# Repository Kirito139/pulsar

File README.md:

Pulsar is a rather simple (its my first ever hardware project) macropad which I made for [highway.hackclub.com](highway.hackclub.com). It features a 3x3 electrical matrix arranged into a 2x4 key grid and a rotary encoder. There's also an OLED display and two NeoPixels! Rather simple design but I'll probably come back and improve it sometime.

# Images

# BOM
I will 3d print the case myself.

Here's the BOM that KiCad generated:

|   |   |   |   |   |   |   |   |
|---|---|---|---|---|---|---|---|
|**Reference**|**Qty**|**Value**|**DNP**|**Exclude from BOM**|**Exclude from Board**|**Footprint**|**Datasheet**|
|**D1,D2**|2|SK6812MINI||||LED_SMD:LED_SK6812MINI_PLCC4_3.5x3.5mm_P1.75mm|[https://cdn-shop.adafruit.com/product-files/2686/SK6812MINI_REV.01-1-2.pdf](https://cdn-shop.adafruit.com/product-files/2686/SK6812MINI_REV.01-1-2.pdf)|
|**D3,D4,D5,D6,D7,D8,D9,D10,D11**|9|1N4148||||Diode_THT:D_DO-35_SOD27_P7.62mm_Horizontal|[https://assets.nexperia.com/documents/data-sheet/1N4148_1N4448.pdf](https://assets.nexperia.com/documents/data-sheet/1N4148_1N4448.pdf)|
|**J1**|1|Conn_01x04_Pin||||hackpad:SSD1306-0.91-OLED-4pin-128x32|~|
|**SW1,SW2,SW3,SW4,SW5,SW7,SW8,SW9**|8|SW_Push||||Button_Switch_Keyboard:SW_Cherry_MX_1.00u_PCB|~|
|**SW6**|1|RotaryEncoder_Switch||||Rotary_Encoder:RotaryEncoder_Alps_EC11E-Switch_Vertical_H20mm|~|
|**U1**|1|XIAO-RP2040-DIP||||OPL:XIAO-RP2040-DIP||

I will also need 4 m3.5 screws

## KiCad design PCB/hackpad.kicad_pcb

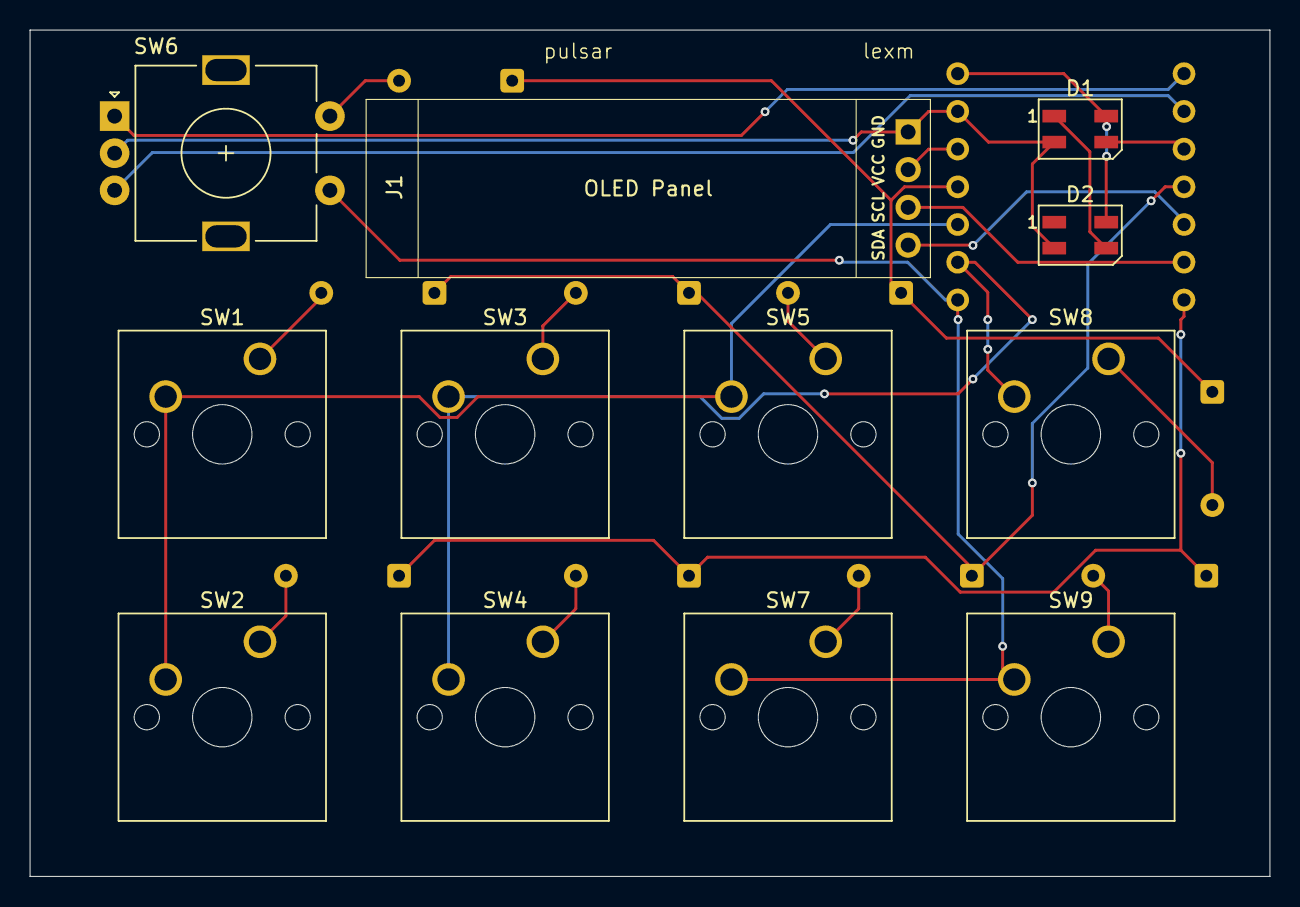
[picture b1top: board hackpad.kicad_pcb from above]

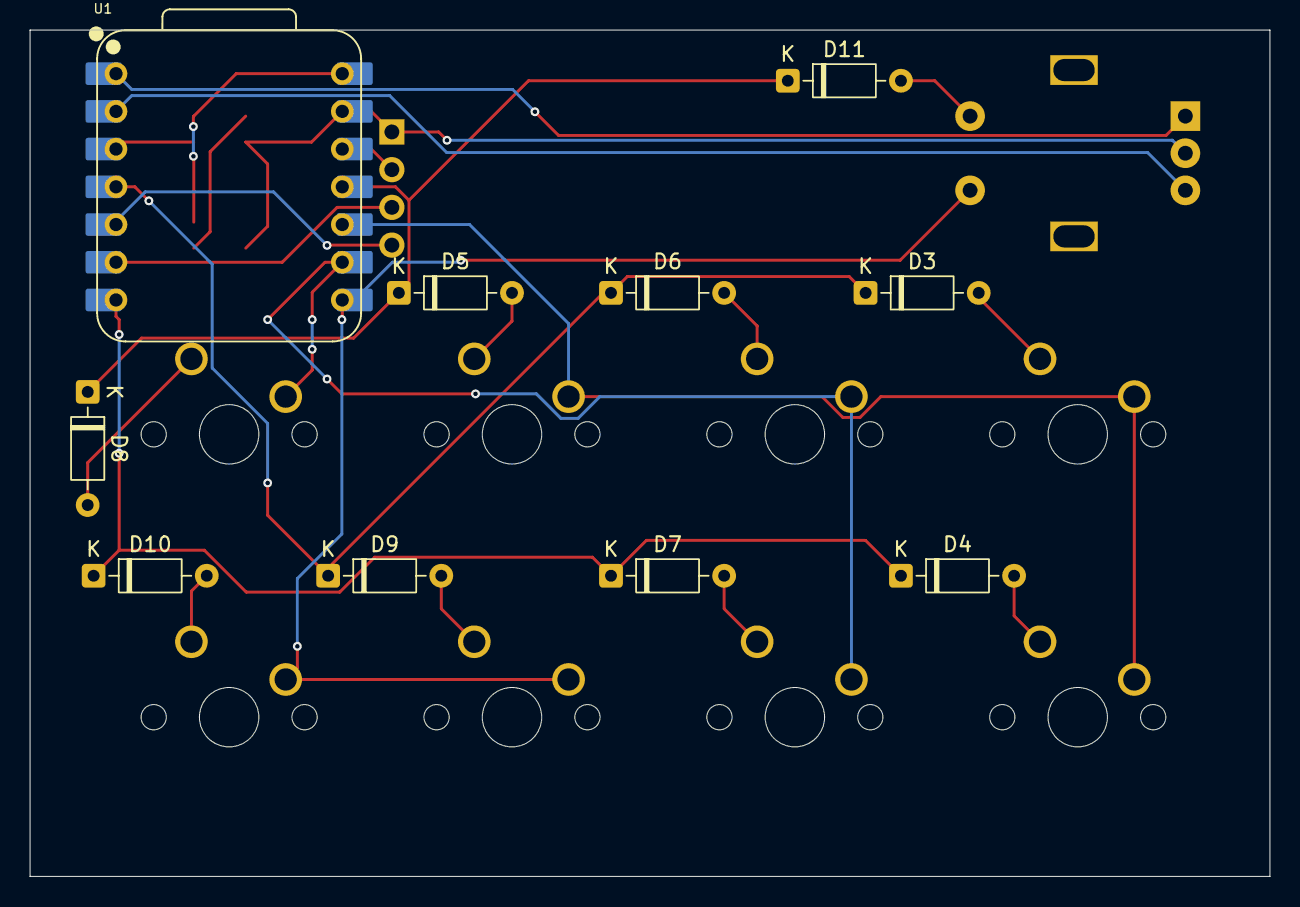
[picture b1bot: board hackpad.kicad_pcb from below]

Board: 2 copper layers, 83.5 x 57.0 mm, 22 parts (10 on the bottom side), 24 nets.

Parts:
D1, D2: SK6812MINI; LED_SK6812MINI_PLCC4_3.5x3.5mm_P1.75mm
D3, D4, D5, D6, D7, D8, D9, D10, D11: 1N4148; D_DO-35_SOD27_P7.62mm_Horizontal
J1: Conn_01x04_Pin; SSD1306-0.91-OLED-4pin-128x32
SW1, SW2, SW3, SW4, SW5, SW7, SW8, SW9: SW_Push; SW_Cherry_MX_1.00u_PCB
SW6: RotaryEncoder_Switch; RotaryEncoder_Alps_EC11E-Switch_Vertical_H20mm
U1: XIAO-RP2040-DIP

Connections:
+3V3: J1.2, U1.12 (3V3)
+5V: D1.4 (VDD), D2.4 (VDD), U1.14 (VBUS)
C1: SW1.2, SW2.2, SW5.2, U1.10 (GPIO4/MISO)
C2: SW3.2, SW4.2, SW8.2, U1.9 (GPIO2/SCK)
C3: SW6.S1, SW7.2, SW9.2, U1.8 (GPIO1/RX)
GND: D1.2 (VSS), D2.2 (VSS), J1.1, SW6.C, U1.13 (GND)
unnamed: D1.3 (DIN), U1.3 (GPIO28/ADC2/A2)
unnamed: D1.1 (DOUT), D2.3 (DIN)
unnamed: D3.2 (A), SW1.1
unnamed: D4.2 (A), SW2.1
unnamed: D5.2 (A), SW5.1
unnamed: D6.2 (A), SW3.1
unnamed: D7.2 (A), SW4.1
unnamed: D8.2 (A), SW8.1
unnamed: D9.2 (A), SW7.1
unnamed: D10.2 (A), SW9.1
unnamed: J1.3, U1.6 (GPIO7/SCL)
unnamed: J1.4, U1.5 (GPIO6/SDA)
unnamed: SW6.A, U1.1 (GPIO26/ADC0/A0)
unnamed: SW6.B, U1.2 (GPIO27/ADC1/A1)
R1: D3.1 (K), D6.1 (K), D9.1 (K), U1.4 (GPIO29/ADC3/A3)
R2: D4.1 (K), D7.1 (K), D10.1 (K), U1.7 (GPIO0/TX)
R3: D5.1 (K), D8.1 (K), D11.1 (K), U1.11 (GPIO3/MOSI)
ROT_B: D11.2 (A), SW6.S2

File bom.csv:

"Reference","Qty","Value","DNP","Exclude from BOM","Exclude from Board","Footprint","Datasheet"
"D1,D2","2","SK6812MINI","","","","LED_SMD:LED_SK6812MINI_PLCC4_3.5x3.5mm_P1.75mm","https://cdn-shop.adafruit.com/product-files/2686/SK6812MINI_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"
"D3,D4,D5,D6,D7,D8,D9,D10,D11","9","1N4148","","","","Diode_THT:D_DO-35_SOD27_P7.62mm_Horizontal","https://assets.nexperia.com/documents/data-sheet/1N4148_1N4448.pdf"
"J1","1","Conn_01x04_Pin","","","","hackpad:SSD1306-0.91-OLED-4pin-128x32","~"
"SW1,SW2,SW3,SW4,SW5,SW7,SW8,SW9","8","SW_Push","","","","Button_Switch_Keyboard:SW_Cherry_MX_1.00u_PCB","~"
"SW6","1","RotaryEncoder_Switch","","","","Rotary_Encoder:RotaryEncoder_Alps_EC11E-Switch_Vertical_H20mm","~"
"U1","1","XIAO-RP2040-DIP","","","","OPL:XIAO-RP2040-DIP",""

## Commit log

2025-07-09 init
2025-07-10 moving stuff around
